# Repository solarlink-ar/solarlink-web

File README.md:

<div align="center">

# Proyecto Solar Link

| Página web | Email | Instagram |
|------------|-------|-----------|
|[Página Web](https://www.solarlink.ar)|info@solarlink.ar|[@solarlink.ar](https://www.instagram.com/solarlink.ar/)|

</div>

## ¿Qué es Solar Link?
&nbsp;&nbsp;&nbsp;&nbsp;&nbsp;&nbsp;Solar Link es un sistema inteligente que optimiza el uso de una energía renovable (por ejemplo, energía solar mediante paneles solares), de manera tal que siempre intentará usar toda la capacidad instalada para ahorrar energía y no consumirla de la red. Es un sistema microprocesado, con conexión a internet y adicionalmente se diseñará una aplicación que  le comunicará al usuario si está ahorrando, cuanto ahorró y una estimación de cuanto ahorrará según el pronóstico del clima.<br>
&nbsp;&nbsp;&nbsp;&nbsp;&nbsp;&nbsp;Dentro los sistemas solares, existen los sistemas *On-grid* y *Off-grid*, mientras que Solar Link es un ***Smart-Grid*** que combina ambos tipos. Este equipo monitorea constantemente el consumo de las líneas eléctricas del hogar y mientras pueda alimentarlas con energía renovables, lo hará posible.<br>
## ¿Cómo ayuda al usuario?
&nbsp;&nbsp;&nbsp;&nbsp;&nbsp;&nbsp;La aplicación móvil que queremos desarrollar le comunicará al usuario toda la información recopilada sobre la red eléctrica. Por ejemplo, podría informar en tiempo real el consumo de la casa, que parte del consumo total de la casa fue proporcionado por energías renovables, o recomendaciones para incrementar el ahorro de energía. De esta manera, el usuario sabrá con certeza el aporte del sistema de energías renovables en el que invirtió.<br>
## ¿Qué aporta a la sociedad?
&nbsp;&nbsp;&nbsp;&nbsp;&nbsp;&nbsp;Consideramos que nuestro proyecto aporta fuertemente a reducir la huella de carbono, ahorrar dinero e incentivar al usuario al uso de este tipo de energías que poco se habla y poco uso hay en Argentina.<br>
## ¿En qué trabajamos?
&nbsp;&nbsp;&nbsp;&nbsp;&nbsp;&nbsp;Nosotros nos encargamos del diseño y la planificación de los diferentes sistemas que forman parte de Solar Link, como el desarrollo íntegro de las placas y los circuitos, la programación del microprocesador, así como la aplicación en su totalidad. Esto conlleva mucho trabajo y esfuerzo de nuestra parte, puesto que siempre buscamos la excelencia en todo lo que hacemos.<br>

## Integrantes:
<div align="center">

</div>

### Iván Ezequiel Cenyko
Programación en microPython y desarrollo web Back-End.

- 📷 Instagram: @ivancenyko

- 📧 ivancenyko@gmail.com

- LinkedIn: [Ivan Cenyko](http://www.linkedin.com/in/ivan-cenyko/)

### Lara Paloma Dias
Desarrollo web Front-End.

- 📷 Instagram: @palo.dias

- 📧 palomadias308@gmail.com

- LinkedIn: [Lara Paloma Dias](http://www.linkedin.com/in/lara-paloma-dias-598bb9288/)

### Mateo Inza Fior
Desarrollo web Front-End y programación en microPython.

- 📷 Instagram: @mateoinzafior

- 📧 mateoinzafior@gmail.com

- LinkedIn: [Mateo Inza Fior](http://www.linkedin.com/in/mateoinzafior/)

### Agustín Palmieri Hise
Desarrollo eléctrico y electrónico íntegro, y documentación.

- 📷 Instagram: @aguspalmieri780

- 📧 aguspalmierihise@gmail.com

- LinkedIn: [Agustin Palmieri Hise](http://www.linkedin.com/in/agustin-palmieri-hise/)

### Maximiliano Nicolás Testa
Programación en C y desarrollo Front-End de la Web-app

- 📷 Instagram: @testa_45

- 📧 maxitesta2012@gmail.com

- LinkedIn: [Maximiliano Testa](http://www.linkedin.com/in/maximiliano-testa/)

## Contactanos

### Instagram: [@solarlink.ar](https://www.instagram.com/solarlink.ar/)

### Pagina web: [solarlink.ar](https://www.solarlink.ar)

### Mail: info@solarlink.ar

### LinkedIn: [Solar Link](https://www.linkedin.com/company/solarlink-ar/?lipi=urn%3Ali%3Apage%3Ad_flagship3_search_srp_all%3BkHWPFMi%2BQiSqZ7LunD5%2FrA%3D%3D)

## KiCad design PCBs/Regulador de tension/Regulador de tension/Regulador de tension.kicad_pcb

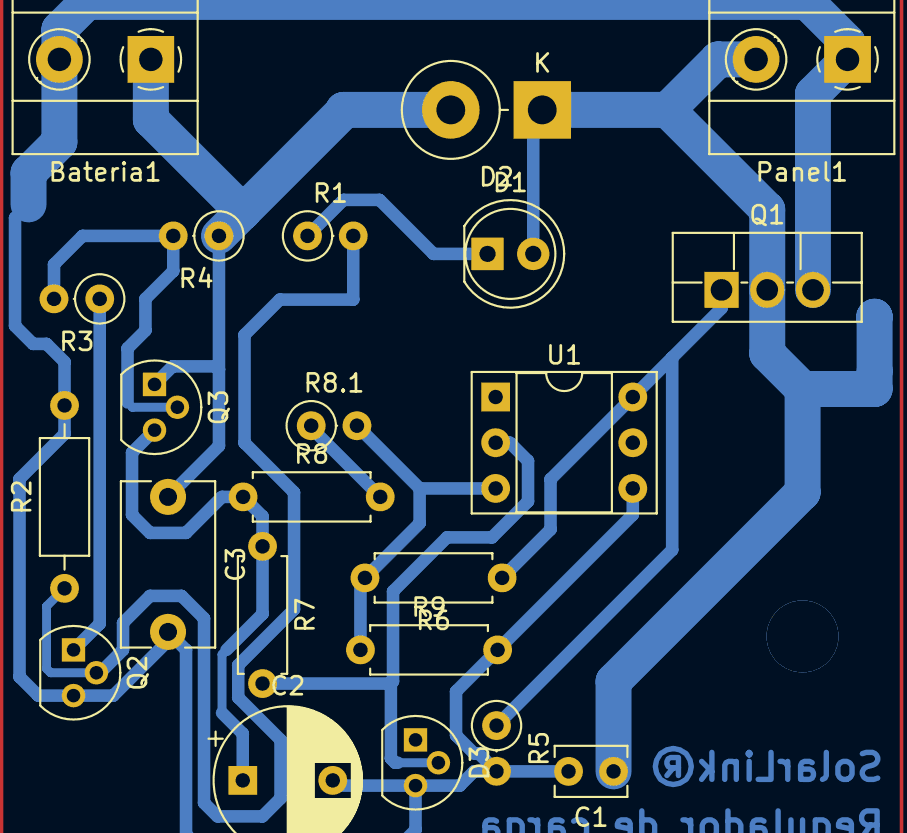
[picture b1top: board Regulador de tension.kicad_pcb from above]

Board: 2 copper layers, 22 parts (0 on the bottom side), 12 nets.

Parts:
Bateria1: Conn_01x02; TerminalBlock_Phoenix_MKDS-1,5-2-5.08_1x02_P5.08mm_Horizont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
C1: 100n; C_Disc_D3.8mm_W2.6mm_P2.50mm
C2: 1000u; CP_Radial_D8.0mm_P5.00mm
C3: 100n; C_Disc_D9.0mm_W5.0mm_P7.50mm
D1: LED; LED_D5.0mm
D2: SB540; D_DO-201AD_P5.08mm_Vertical_KathodeUp
D3: LM385BZ-2.5; TO-92
Panel1: Conn_01x02; TerminalBlock_Phoenix_MKDS-1,5-2-5.08_1x02_P5.08mm_Horizont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
Q1: BUZ11; TO-220F-3_Vertical
Q2: BC548; TO-92
Q3: BC556; TO-92
R1: 1k5; R_Axial_DIN0207_L6.3mm_D2.5mm_P2.54mm_Vertical
R2: 100; R_Axial_DIN0207_L6.3mm_D2.5mm_P10.16mm_Horizontal
R3: 68k; R_Axial_DIN0207_L6.3mm_D2.5mm_P2.54mm_Vertical
R4, R5, R8.1: 10k; R_Axial_DIN0207_L6.3mm_D2.5mm_P2.54mm_Vertical
R6: 22Ok; R_Axial_DIN0207_L6.3mm_D2.5mm_P7.62mm_Horizontal
R7: 100k; R_Axial_DIN0207_L6.3mm_D2.5mm_P7.62mm_Horizontal
R8: 82k; R_Axial_DIN0207_L6.3mm_D2.5mm_P7.62mm_Horizontal
R9: 22k; R_Axial_DIN0207_L6.3mm_D2.5mm_P7.62mm_Horizontal
U1: TLC271; DIP-6_W7.62mm_Socket

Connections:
GND: Bateria1.2, C1.2, C2.2, C3.2, D3.3 (A), Panel1.1, Q1.3 (S), Q2.3 (E), R2.2, R5.2, R9.2, U1.4 (V-)
unnamed: Bateria1.1, C3.1, D2.2 (A), Q3.1 (C), R4.1
unnamed: C1.1, D1.2 (A), D2.1 (K), Panel1.2, Q1.2 (D)
unnamed: C2.1, Q3.3 (E), R7.1, R8.1
unnamed: D1.1 (K), R1.1
unnamed: D3.2 (K), R7.2, U1.2 (-)
unnamed: Q1.1 (G), R5.1, R6.1, U1.6
unnamed: Q2.1 (C), R3.1
unnamed: Q2.2 (B), R1.2, R2.1
unnamed: Q3.2 (B), R3.2, R4.2
unnamed: R8.2, R8.1.1
unnamed: R6.2, R8.1.2, R9.1, U1.3 (+)

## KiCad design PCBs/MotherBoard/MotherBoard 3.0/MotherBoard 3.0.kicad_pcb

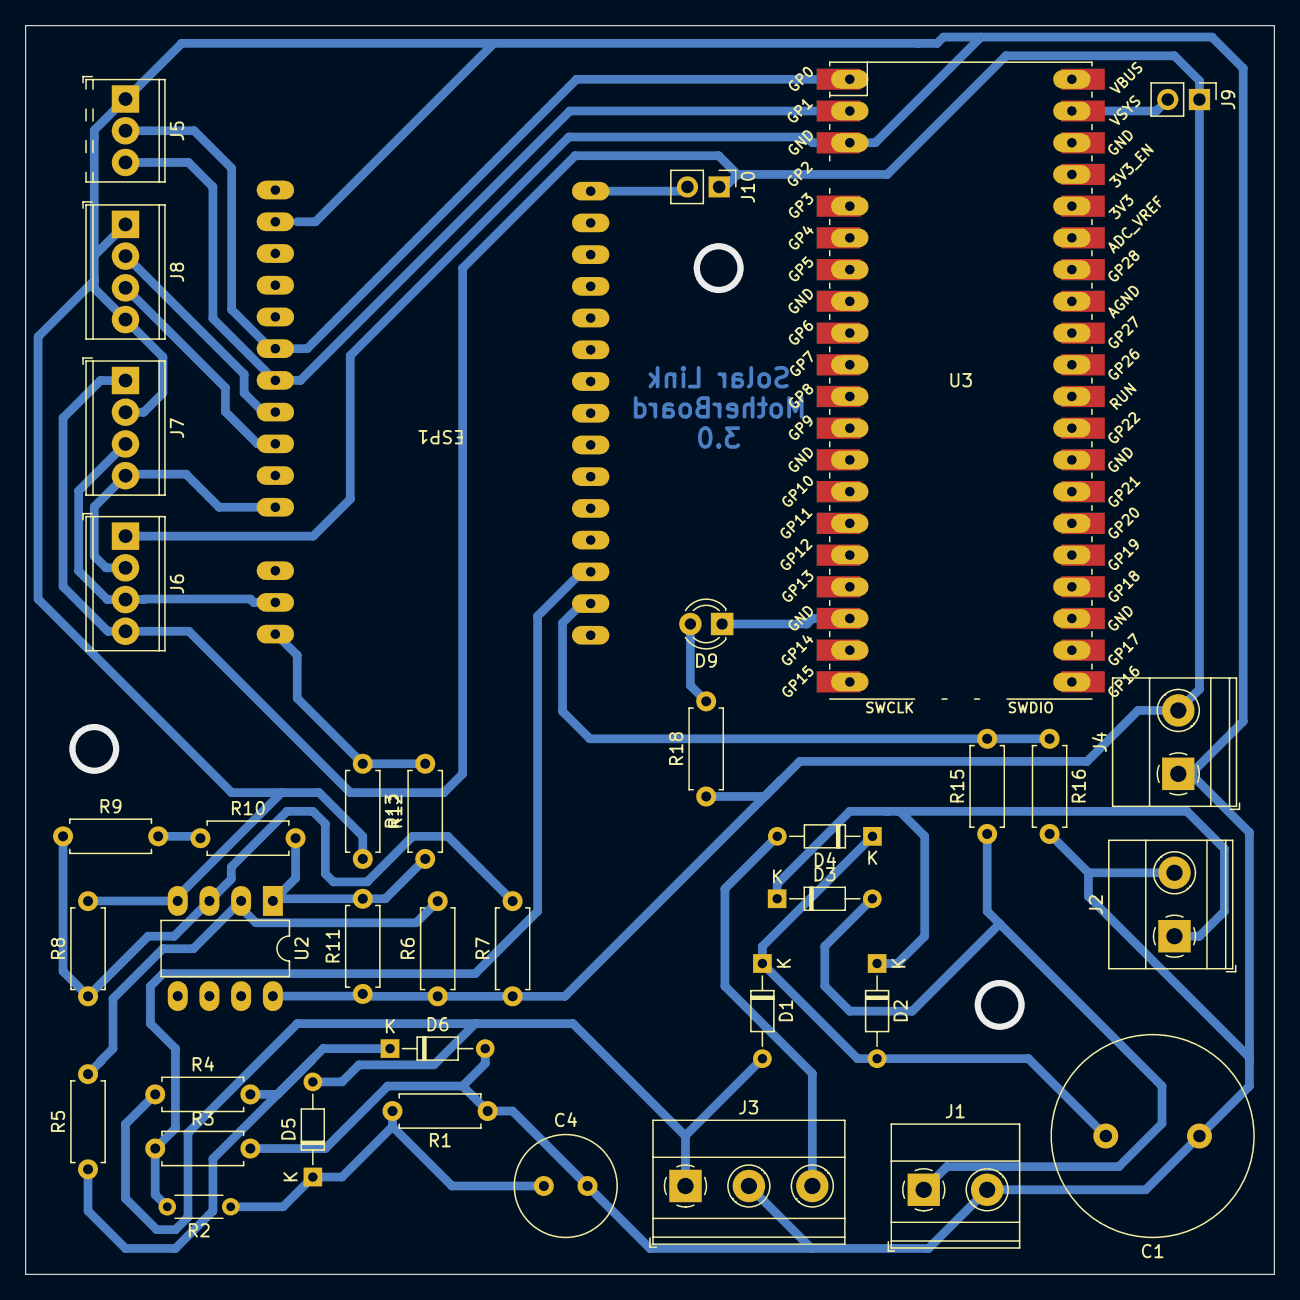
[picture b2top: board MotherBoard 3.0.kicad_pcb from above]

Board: 2 copper layers, 100.0 x 100.0 mm, 38 parts (0 on the bottom side), 26 nets.

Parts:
C1: 2200uF; C_Radial_D16.0mm_H25.0mm_P7.50mm
C4: 100u; C_Radial_D8.0mm_H11.5mm_P3.50mm
D1, D2, D3, D4, D5: D; D_DO-34_SOD68_P7.62mm_Horizontal
D6: 1N914; D_DO-34_SOD68_P7.62mm_Horizontal
D9: Verde; LED_D3.0mm
ESP1: ESP32 15pin
J1: Bateria; TerminalBlock_Phoenix_MKDS-1,5-2-5.08_1x02_P5.08mm_Horizont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
J2: Salida 12V; TerminalBlock_Phoenix_MKDS-1,5-2-5.08_1x02_P5.08mm_Horizont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
J3: Transformador; TerminalBlock_Phoenix_MKDS-1,5-3-5.08_1x03_P5.08mm_Horizont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
J4: Salida 5v; TerminalBlock_Phoenix_MKDS-1,5-2-5.08_1x02_P5.08mm_Horizont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
J5: Raspberry Pi; TerminalBlock_Phoenix_MPT-0,5-3-2.54_1x03_P2.54mm_Horizontal
J6: LCD; TerminalBlock_Phoenix_MPT-0,5-4-2.54_1x04_P2.54mm_Horizontal
J7: Corriente; TerminalBlock_Phoenix_MPT-0,5-4-2.54_1x04_P2.54mm_Horizontal
J8: Conmutacion; TerminalBlock_Phoenix_MPT-0,5-4-2.54_1x04_P2.54mm_Horizontal
J9, J10: Conn_01x02_Pin; PinHeader_1x02_P2.54mm_Vertical
R1, R3, R8, R16: 10k; R_Axial_DIN0207_L6.3mm_D2.5mm_P7.62mm_Horizontal
R2: 220k; R_Axial_DIN0204_L3.6mm_D1.6mm_P5.08mm_Horizontal
R4, R5, R11: 5,1k; R_Axial_DIN0207_L6.3mm_D2.5mm_P7.62mm_Horizontal
R6, R7, R12, R15: 100k; R_Axial_DIN0207_L6.3mm_D2.5mm_P7.62mm_Horizontal
R9, R10: 10M; R_Axial_DIN0207_L6.3mm_D2.5mm_P7.62mm_Horizontal
R13: 150k; R_Axial_DIN0207_L6.3mm_D2.5mm_P7.62mm_Horizontal
R18: 1k; R_Axial_DIN0207_L6.3mm_D2.5mm_P7.62mm_Horizontal
U2: AD8603; DIP-8_W7.62mm_LongPads
U3: Pico; RPi_Pico_SMD_TH

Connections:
Bat 1: D3.2 (A), J1.1, R15.1
Bat 2: C1.1, C4.2, D6.2 (A), ESP1.29 (GPIO0,RTC_GPIO11,ADC2_1,TOUCH_1), J1.2, J2.2, J3.2, J4.1, J5.1, J6.1, J7.2, J8.1, J8.4, R1.1, R3.2, R8.2, R13.2, R16.2, U2.4 (V-), U3.3 (GND)
ESP1, ADC: ESP1.3 (ADC1_0,RTC_GPIO0,GPIO36), R2.2, R3.1
ESP2: ESP1.16 (GND), R12.2, R13.1
ESP3, I/O: ESP1.23 (GPIO19,VSPI_MISO), J8.2
ESP4, I/O: ESP1.22 (GND), J8.3
ESP5, SDA: ESP1.20 (GPIO3,RX0), J6.2, J7.4
ESP6, SCL: ESP1.17 (GPIO23,VSPI_MOSI), J6.3, J7.3
ESP7, Rx: ESP1.25 (GPIO5,VSPI_CS), J5.2, U3.1 (GPIO0)
ESP8, Tx: ESP1.24 (GPIO18,VSPI_CLK), J5.3, U3.2 (GPIO1)
ESP 12, ADC: ESP1.2 (Reset,En), R15.2, R16.1
Fuente 5v: J4.2, J6.4, J7.1, J9.1, J10.1, R6.1, R7.1, R11.1, R18.1, U2.8 (V+)
Fuente 12v: D2.1 (K), D3.1 (K), J2.1
GNDREF: D9.1 (K), U3.18 (GND)
unnamed: C1.2, D1.1 (K), D2.2 (A), D4.1 (K)
unnamed: C4.1, D5.1 (K), R1.2, R2.1
unnamed: D6.1 (K), R4.2, R5.1
unnamed: D9.2 (A), R18.2
unnamed: ESP1.15 (ADC2_4,RTCGPIO14,GPIO13,TOUCH_4,HSPI_MO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), J10.2
unnamed: J9.2, U3.39 (VSYS)
unnamed: R9.2, R10.1
unnamed: R10.2, R11.2, R12.1, U2.1
unnamed: R7.2, R8.1, R9.1, U2.3 (+)
unnamed: R5.2, R6.2, U2.2 (-)
Trans 1: D1.2 (A), D5.2 (A), J3.1, R4.1
Trans 2: D4.2 (A), J3.3

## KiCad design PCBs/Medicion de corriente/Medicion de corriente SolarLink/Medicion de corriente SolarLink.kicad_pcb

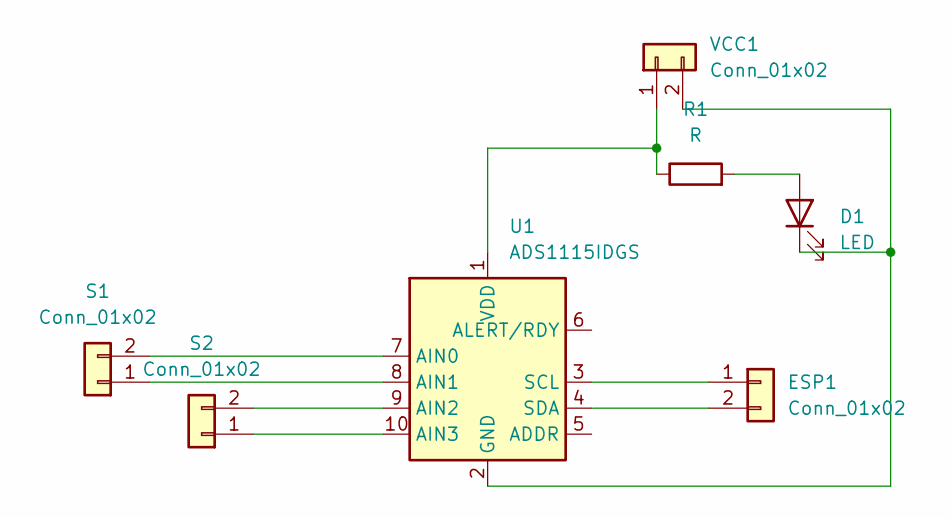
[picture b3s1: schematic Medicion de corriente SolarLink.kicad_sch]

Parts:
D1: LED; LED_D3.0mm
ESP1: Conn_01x02; JST_XH_B2B-XH-AM_1x02_P2.50mm_Vertical
R1: R; R_Axial_DIN0204_L3.6mm_D1.6mm_P5.08mm_Horizontal
S1, S2: Conn_01x02; PinHeader_1x02_P2.54mm_Vertical
U1: ADS1115IDGS; PinHeader_1x10_P2.54mm_Vertical
VCC1: Conn_01x02; JST_XH_B2B-XH-AM_1x02_P2.50mm_Vertical

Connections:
GND: R1.1, U1.1 (VDD), VCC1.1
unnamed: D1.1 (K), U1.2 (GND), VCC1.2
unnamed: D1.2 (A), R1.2
unnamed: ESP1.1, U1.3 (SCL)
unnamed: ESP1.2, U1.4 (SDA)
unnamed: S1.1, U1.8 (AIN1)
unnamed: S1.2, U1.7 (AIN0)
unnamed: S2.1, U1.10 (AIN3)
unnamed: S2.2, U1.9 (AIN2)

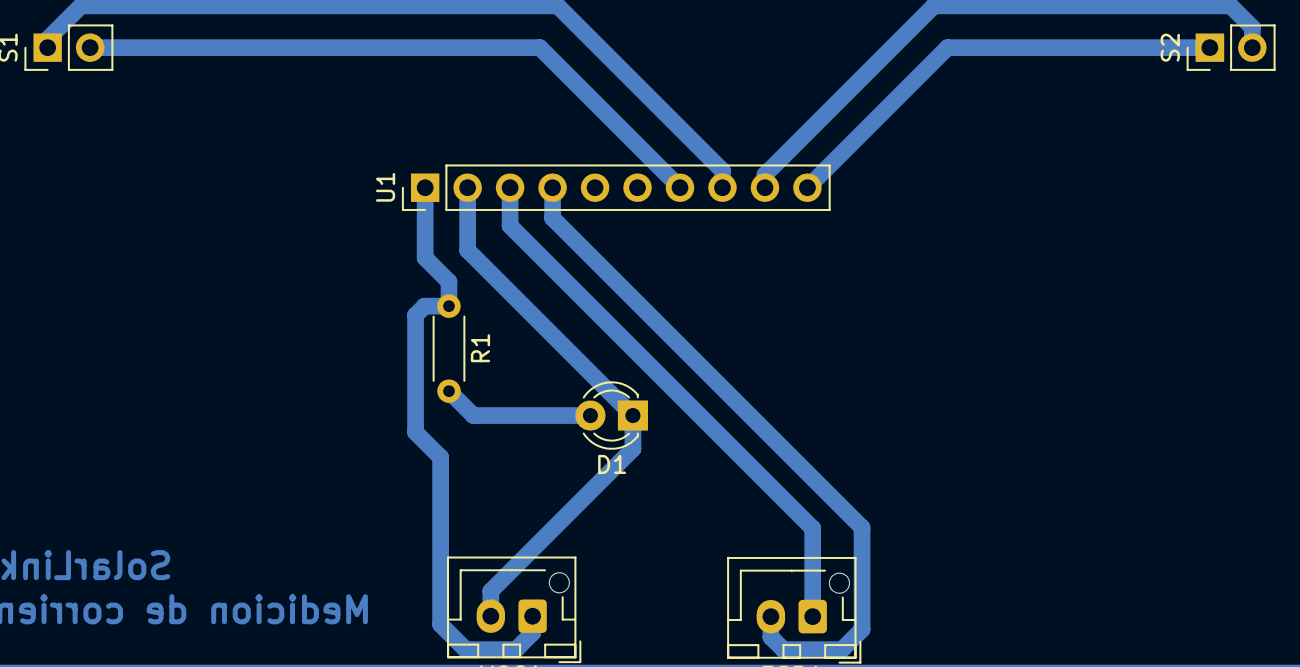
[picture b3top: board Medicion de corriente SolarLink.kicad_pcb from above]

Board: 2 copper layers, 7 parts (0 on the bottom side), 9 nets.

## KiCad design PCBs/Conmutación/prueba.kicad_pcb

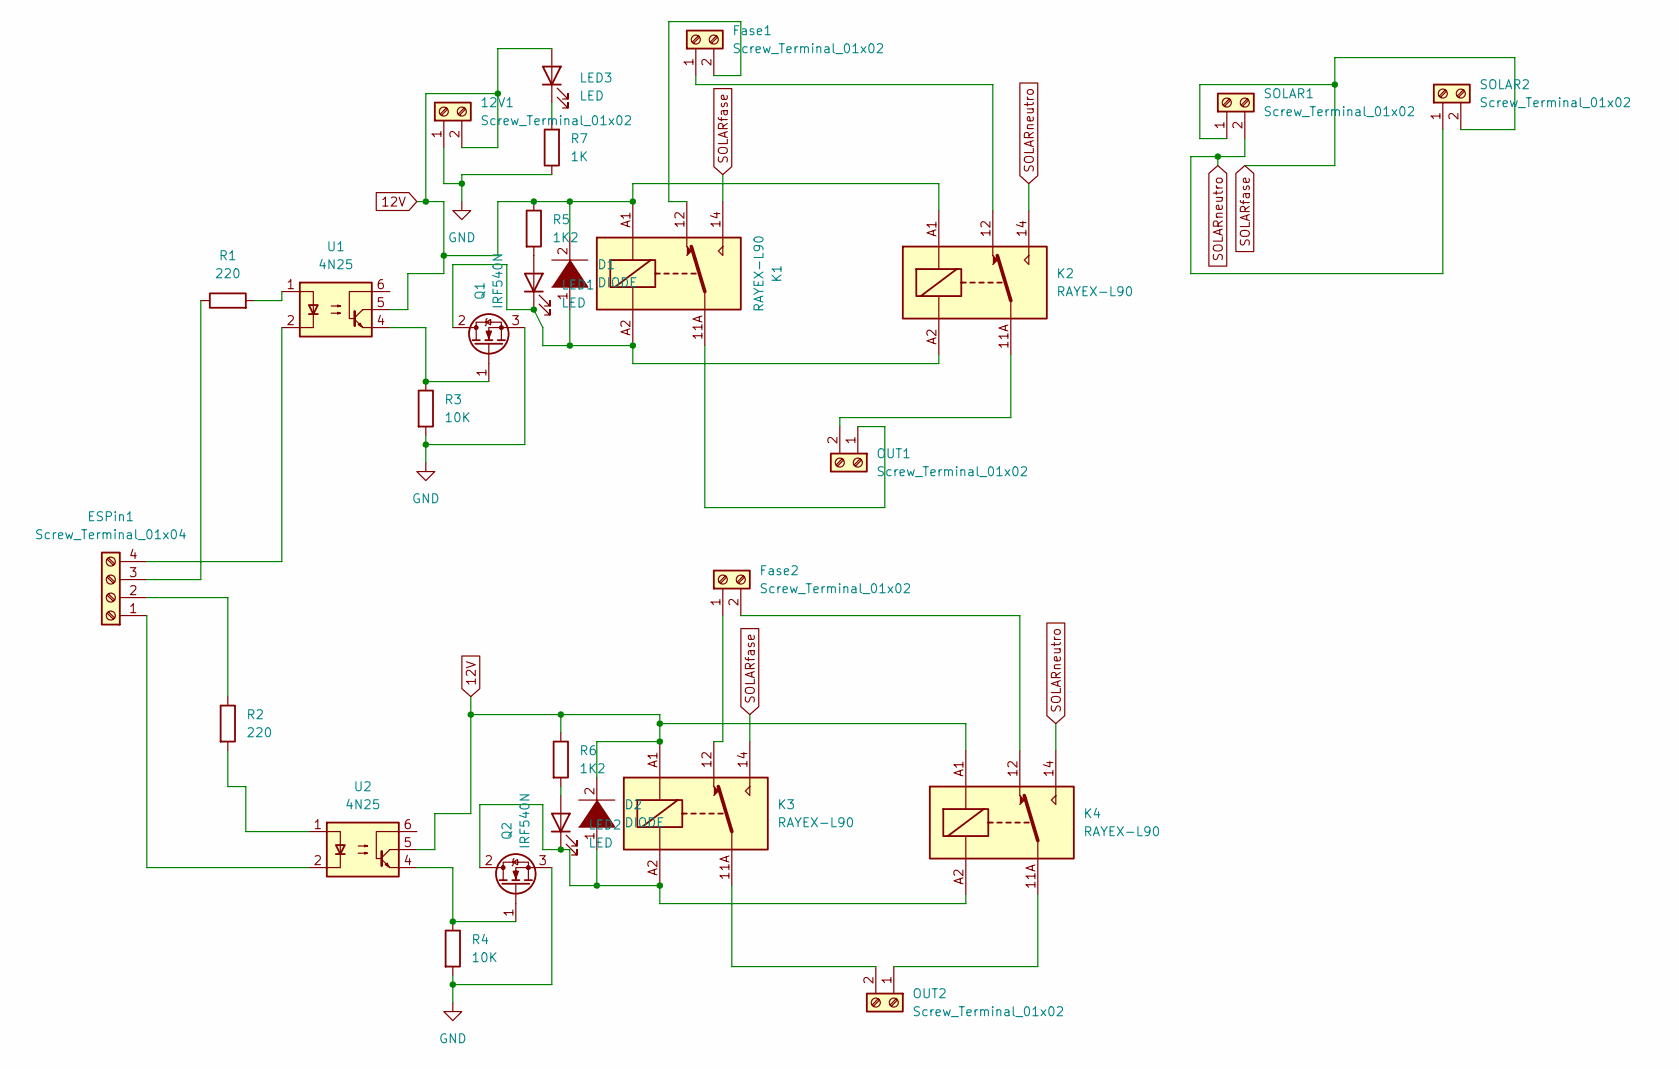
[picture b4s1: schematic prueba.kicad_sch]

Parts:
12V1: Screw_Terminal_01x02; TerminalBlock_Phoenix_MKDS-1,5-2-5.08_1x02_P5.08mm_Horizont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
D1, D2: DIODE; D_DO-201AD_P5.08mm_Vertical_AnodeUp
ESPin1: Screw_Terminal_01x04; TerminalBlock_Phoenix_MPT-0,5-4-2.54_1x04_P2.54mm_Horizontal
Fase1, Fase2: Screw_Terminal_01x02; TerminalBlock_MetzConnect_Type067_RT01902HDWC_1x02_P10.00mm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
K1, K2, K3, K4: RAYEX-L90; Relay_SPDT_RAYEX-L90
LED1, LED2, LED3: LED; LED_D5.0mm
OUT1, OUT2: Screw_Terminal_01x02; TerminalBlock_MetzConnect_Type067_RT01902HDWC_1x02_P10.00mm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
Q1, Q2: IRF540N; TO-220-3_Vertical
R1, R2: 220; R_Axial_DIN0207_L6.3mm_D2.5mm_P7.62mm_Horizontal
R3, R4: 10K; R_Axial_DIN0411_L9.9mm_D3.6mm_P5.08mm_Vertical
R5, R6: 1K2; R_Axial_DIN0207_L6.3mm_D2.5mm_P2.54mm_Vertical
R7: 1K; R_Axial_DIN0207_L6.3mm_D2.5mm_P2.54mm_Vertical
SOLAR1, SOLAR2: Screw_Terminal_01x02; TerminalBlock_MetzConnect_Type067_RT01902HDWC_1x02_P10.00mm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
U1, U2: 4N25; DIP-6_W7.62mm

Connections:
12V: 12V1.2, D1.2 (A), D2.2 (A), K1.A1, K2.A1, K3.A1, K4.A1, LED3.2 (A), R5.1, R6.1, U1.5, U2.5
GND: 12V1.1, Q1.3 (S), Q2.3 (S), R3.2, R4.2, R7.1
unnamed: D1.1 (K), K1.A2, K2.A2, LED1.1 (K), Q1.2 (D)
unnamed: D2.1 (K), K3.A2, K4.A2, LED2.1 (K), Q2.2 (D)
unnamed: ESPin1.1, U2.2
unnamed: ESPin1.2, R2.1
unnamed: ESPin1.3, R1.1
unnamed: ESPin1.4, U1.2
unnamed: Fase1.2, K1.12
unnamed: Fase2.1, K3.12
unnamed: Fase2.2, K4.12
unnamed: K2.11A, K2.11B, OUT1.2
unnamed: Fase1.1, K2.12
unnamed: K3.11A, K3.11B, OUT2.2
unnamed: K4.11A, K4.11B, OUT2.1
unnamed: LED1.2 (A), R5.2
unnamed: LED2.2 (A), R6.2
unnamed: LED3.1 (K), R7.2
unnamed: K1.11A, K1.11B, OUT1.1
unnamed: Q1.1 (G), R3.1, U1.4
unnamed: Q2.1 (G), R4.1, U2.4
unnamed: R1.2, U1.1
unnamed: R2.2, U2.1
SOLARfase: K1.14, K3.14, SOLAR1.1, SOLAR2.2
SOLARneutro: K2.14, K4.14, SOLAR1.2, SOLAR2.1

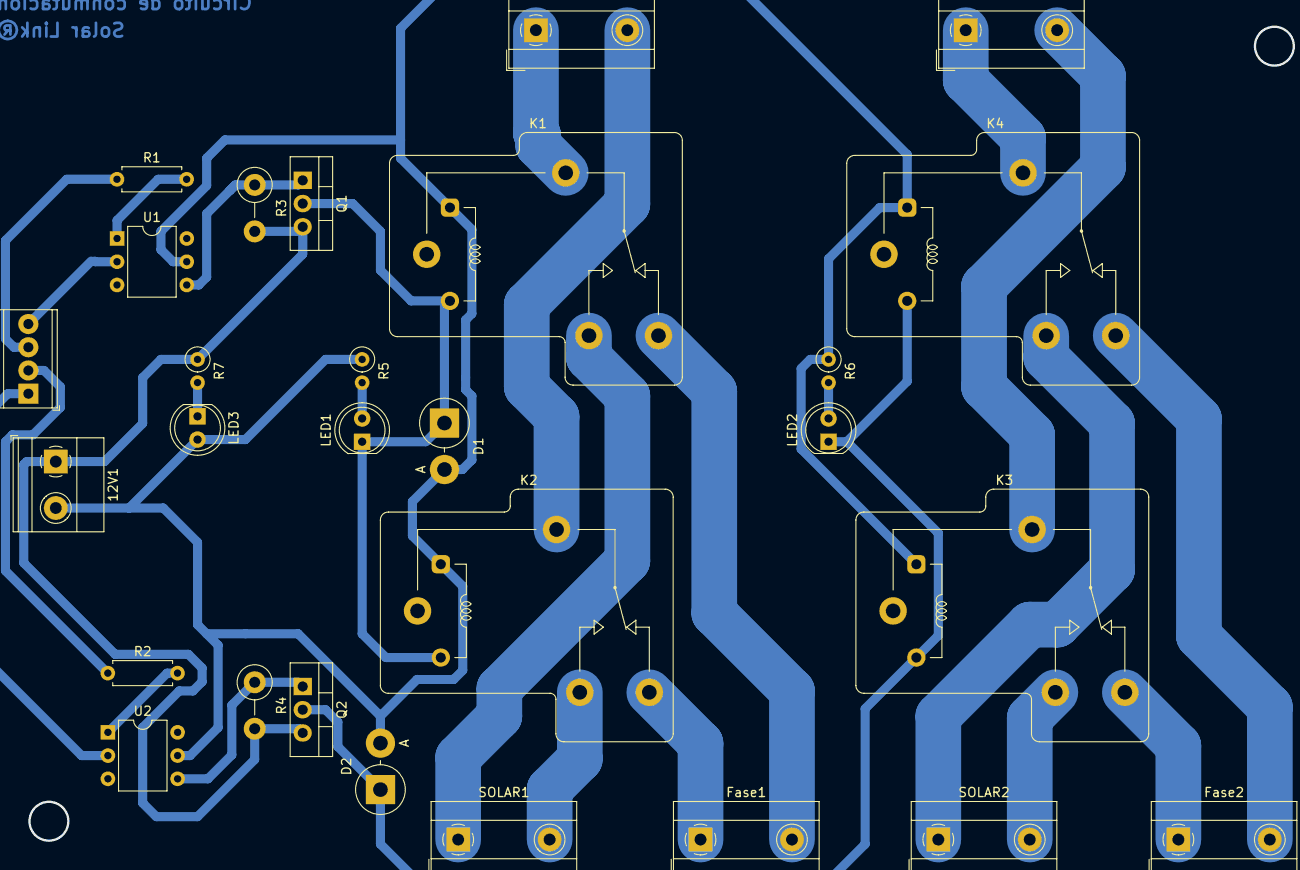
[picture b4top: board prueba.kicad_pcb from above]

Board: 2 copper layers, 28 parts (0 on the bottom side), 25 nets.

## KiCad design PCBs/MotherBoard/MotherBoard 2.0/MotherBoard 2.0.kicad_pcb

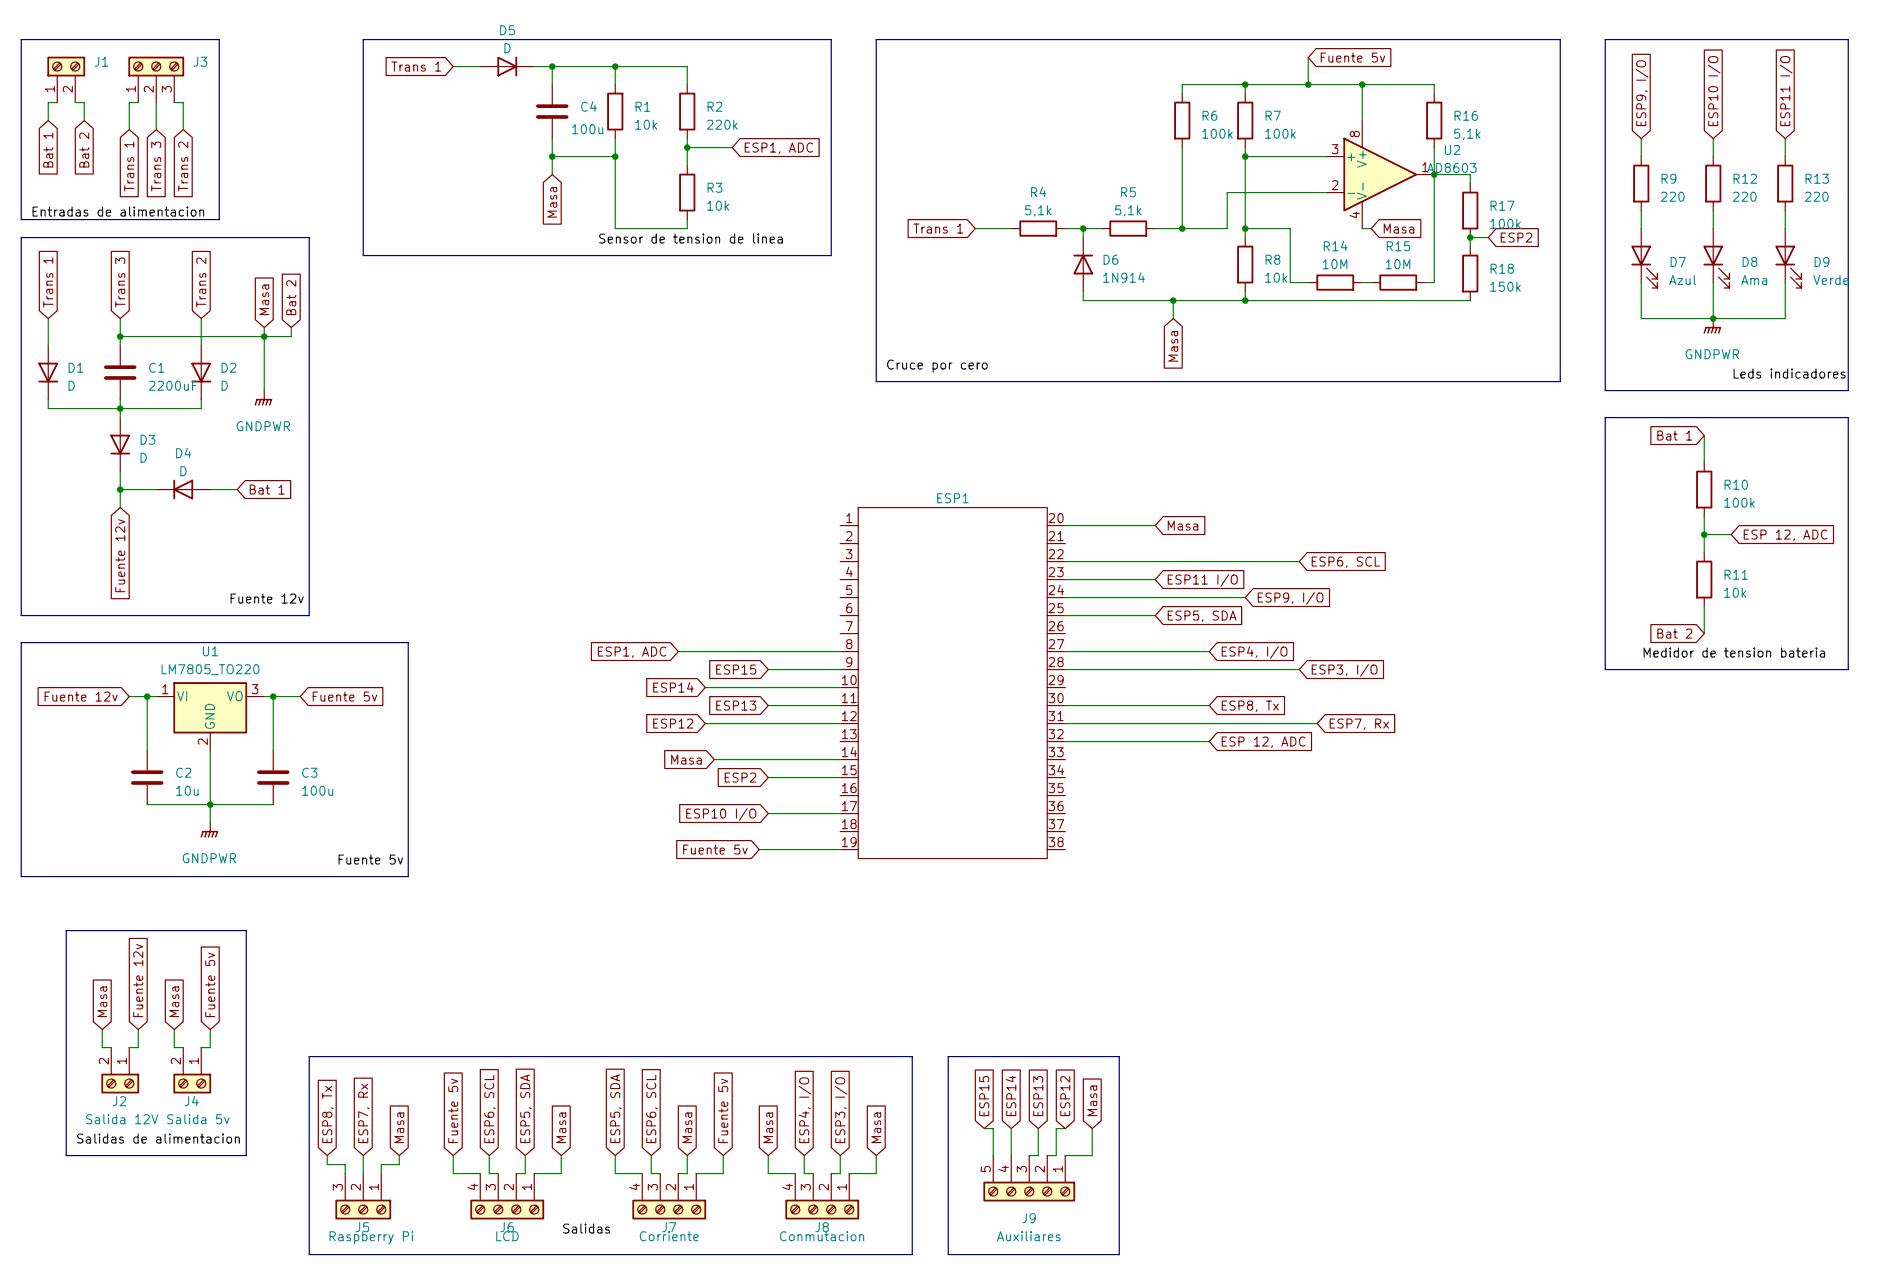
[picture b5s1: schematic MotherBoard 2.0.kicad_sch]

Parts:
C1: 2200uF; C_Radial_D16.0mm_H25.0mm_P7.50mm
C2: 10u; C_Radial_D6.3mm_H11.0mm_P2.50mm
C3, C4: 100u; C_Radial_D8.0mm_H11.5mm_P3.50mm
D1, D2, D3, D4, D5: D; D_DO-34_SOD68_P7.62mm_Horizontal
D6: 1N914; D_DO-34_SOD68_P7.62mm_Horizontal
D7: Azul; LED_D3.0mm
D8: Ama; LED_D3.0mm
D9: Verde; LED_D3.0mm
ESP1: ESP32 NODEMCU
J1: Bateria; TerminalBlock_Phoenix_MKDS-1,5-2-5.08_1x02_P5.08mm_Horizont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
J2: Salida 12V; TerminalBlock_Phoenix_MKDS-1,5-2-5.08_1x02_P5.08mm_Horizont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
J3: Transformador; TerminalBlock_Phoenix_MKDS-1,5-3-5.08_1x03_P5.08mm_Horizont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
J4: Salida 5v; TerminalBlock_Phoenix_MKDS-1,5-2-5.08_1x02_P5.08mm_Horizont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
J5: Raspberry Pi; TerminalBlock_Phoenix_MPT-0,5-3-2.54_1x03_P2.54mm_Horizontal
J6: LCD; TerminalBlock_Phoenix_MPT-0,5-4-2.54_1x04_P2.54mm_Horizontal
J7: Corriente; TerminalBlock_Phoenix_MPT-0,5-4-2.54_1x04_P2.54mm_Horizontal
J8: Conmutacion; TerminalBlock_Phoenix_MPT-0,5-4-2.54_1x04_P2.54mm_Horizontal
J9: Auxiliares; TerminalBlock_Phoenix_MPT-0,5-5-2.54_1x05_P2.54mm_Horizontal
R1, R3, R8, R11: 10k; R_Axial_DIN0207_L6.3mm_D2.5mm_P7.62mm_Horizontal
R2: 220k; R_Axial_DIN0204_L3.6mm_D1.6mm_P5.08mm_Horizontal
R4, R5, R16: 5,1k; R_Axial_DIN0207_L6.3mm_D2.5mm_P7.62mm_Horizontal
R6, R7, R10, R17: 100k; R_Axial_DIN0207_L6.3mm_D2.5mm_P7.62mm_Horizontal
R9, R12, R13: 220; R_Axial_DIN0207_L6.3mm_D2.5mm_P7.62mm_Horizontal
R14, R15: 10M; R_Axial_DIN0207_L6.3mm_D2.5mm_P7.62mm_Horizontal
R18: 150k; R_Axial_DIN0207_L6.3mm_D2.5mm_P7.62mm_Horizontal
U1: LM7805_TO220; TO-220-3_Vertical
U2: AD8603; DIP-8_W7.62mm_LongPads

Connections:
Bat 1: D4.2 (A), J1.1, R10.1
Bat 2: C1.1, C2.2, C3.2, C4.2, D6.2 (A), D7.1 (K), D8.1 (K), D9.1 (K), ESP1.14 (GND), ESP1.20 (GND), J1.2, J2.2, J3.2, J4.2, J5.1, J6.1, J7.2, J8.1, J8.4, J9.1, R1.1, R3.2, R8.2, R11.2, R18.2, U1.2 (GND), U2.4 (V-)
ESP1, ADC: ESP1.8 (ADC1_5,RTCGPIO8,GPIO33,TOUCH_8), R2.2, R3.1
ESP2: ESP1.15 (ADC2_4,RTCGPIO14,GPIO13,TOUCH_4,HSPI_MO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), R17.2, R18.1
ESP3, I/O: ESP1.28 (GPIO18,VSPI_CLK), J8.2
ESP4, I/O: ESP1.27 (GPIO19,VSPI_MISO), J8.3
ESP5, SDA: ESP1.25 (GPIO21,I2C_SDA), J6.2, J7.4
ESP6, SCL: ESP1.22 (GPIO22,I2C_SCL), J6.3, J7.3
ESP7, Rx: ESP1.31 (GPIO16,RX2), J5.2
ESP8, Tx: ESP1.30 (GPIO17,TX2), J5.3
ESP9, I/O: ESP1.24 (GPIO3,RX0), R9.1
ESP10 I/O: ESP1.17 (SWP/SD3,GPIO10), R12.1
ESP11 I/O: ESP1.23 (GPIO1,TX0), R13.1
ESP12: ESP1.12 (ADC2_6,RTCGPIO16,GPIO32,TOUCH_6,HSPI_CL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), J9.2
ESP13: ESP1.11 (ADC2_7,RTCGPIO17,GPIO27,TOUCH_7), J9.3
ESP14: ESP1.10 (ADC2_9,RTCGPIO7,GPIO26,DAC_2), J9.4
ESP15: ESP1.9 (ADC2_8,RTCGPIO8,GPIO25,DAC_1), J9.5
ESP 12, ADC: ESP1.32 (GPIO4,RTC_GPIO10,ADC2_0,TOUCH_0,SD_DAT1), R10.2, R11.1
Fuente 5v: C3.1, ESP1.19 (5v), J4.1, J6.4, J7.1, R6.1, R7.1, R16.1, U1.3 (VO), U2.8 (V+)
Fuente 12v: C2.1, D3.1 (K), D4.1 (K), J2.1, U1.1 (VI)
unnamed: C1.2, D1.1 (K), D2.1 (K), D3.2 (A)
unnamed: C4.1, D5.1 (K), R1.2, R2.1
unnamed: D6.1 (K), R4.2, R5.1
unnamed: D7.2 (A), R9.2
unnamed: D8.2 (A), R12.2
unnamed: D9.2 (A), R13.2
unnamed: R14.2, R15.1
unnamed: R15.2, R16.2, R17.1, U2.1
unnamed: R7.2, R8.1, R14.1, U2.3 (+)
unnamed: R5.2, R6.2, U2.2 (-)
Trans 1: D1.2 (A), D5.2 (A), J3.1, R4.1
Trans 2: D2.2 (A), J3.3

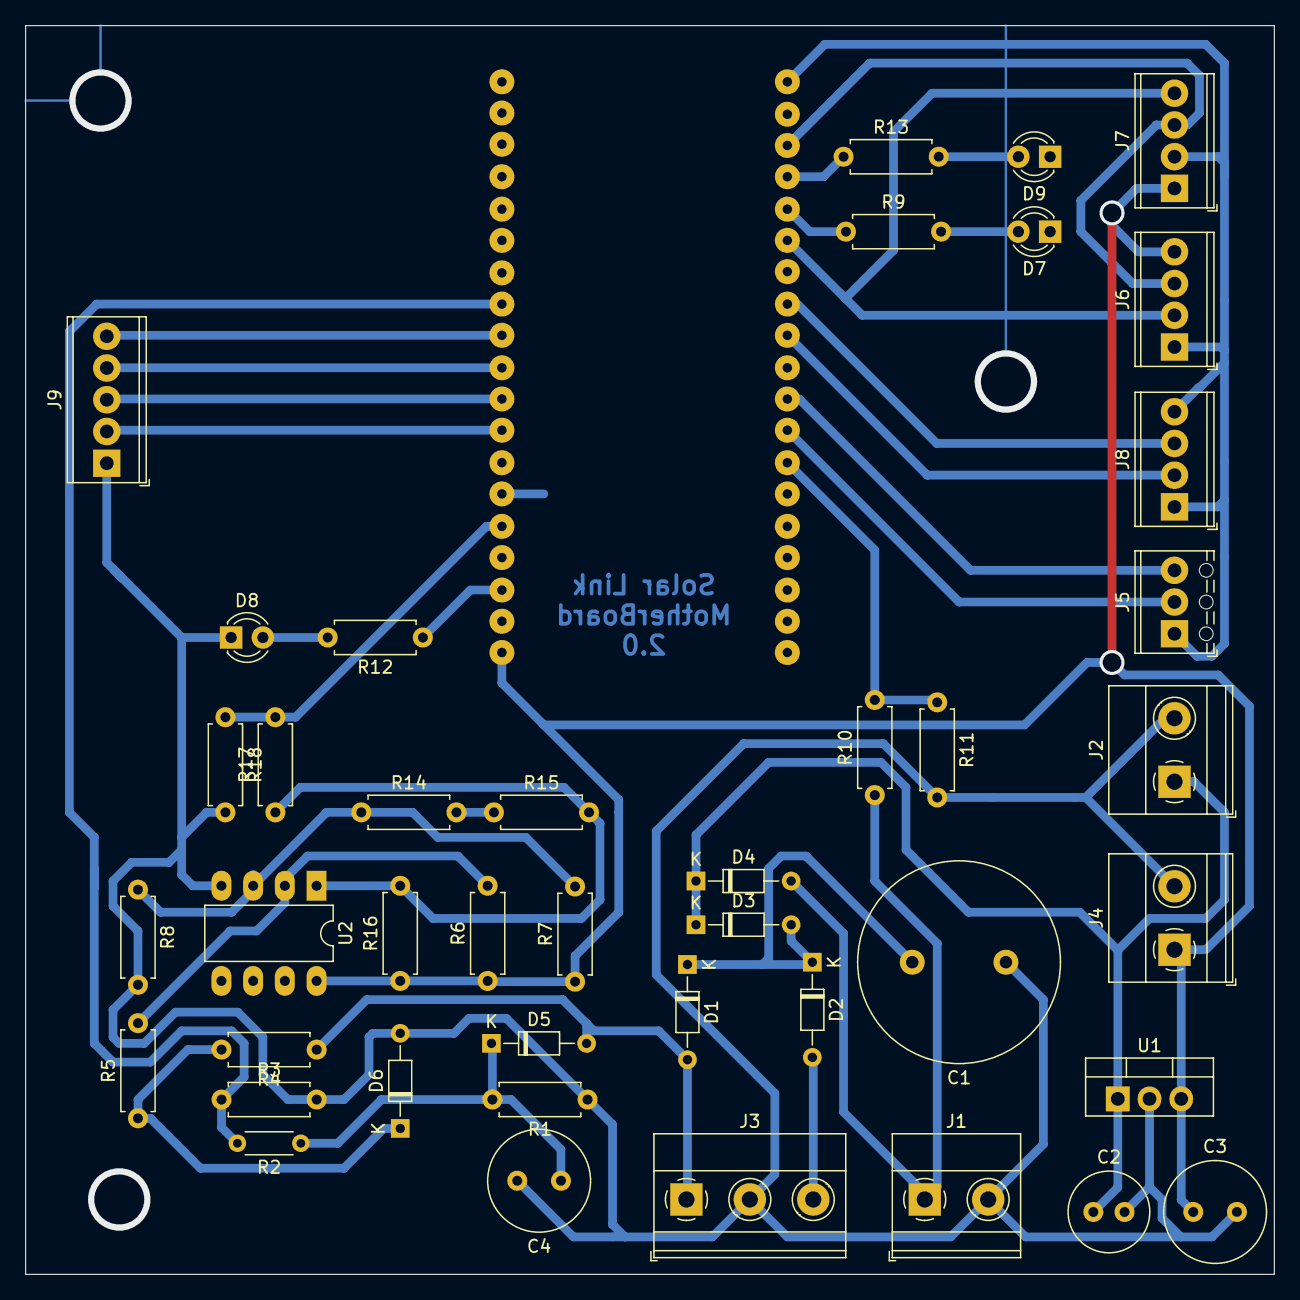
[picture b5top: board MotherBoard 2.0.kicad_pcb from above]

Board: 2 copper layers, 100.0 x 100.0 mm, 43 parts (0 on the bottom side), 32 nets.

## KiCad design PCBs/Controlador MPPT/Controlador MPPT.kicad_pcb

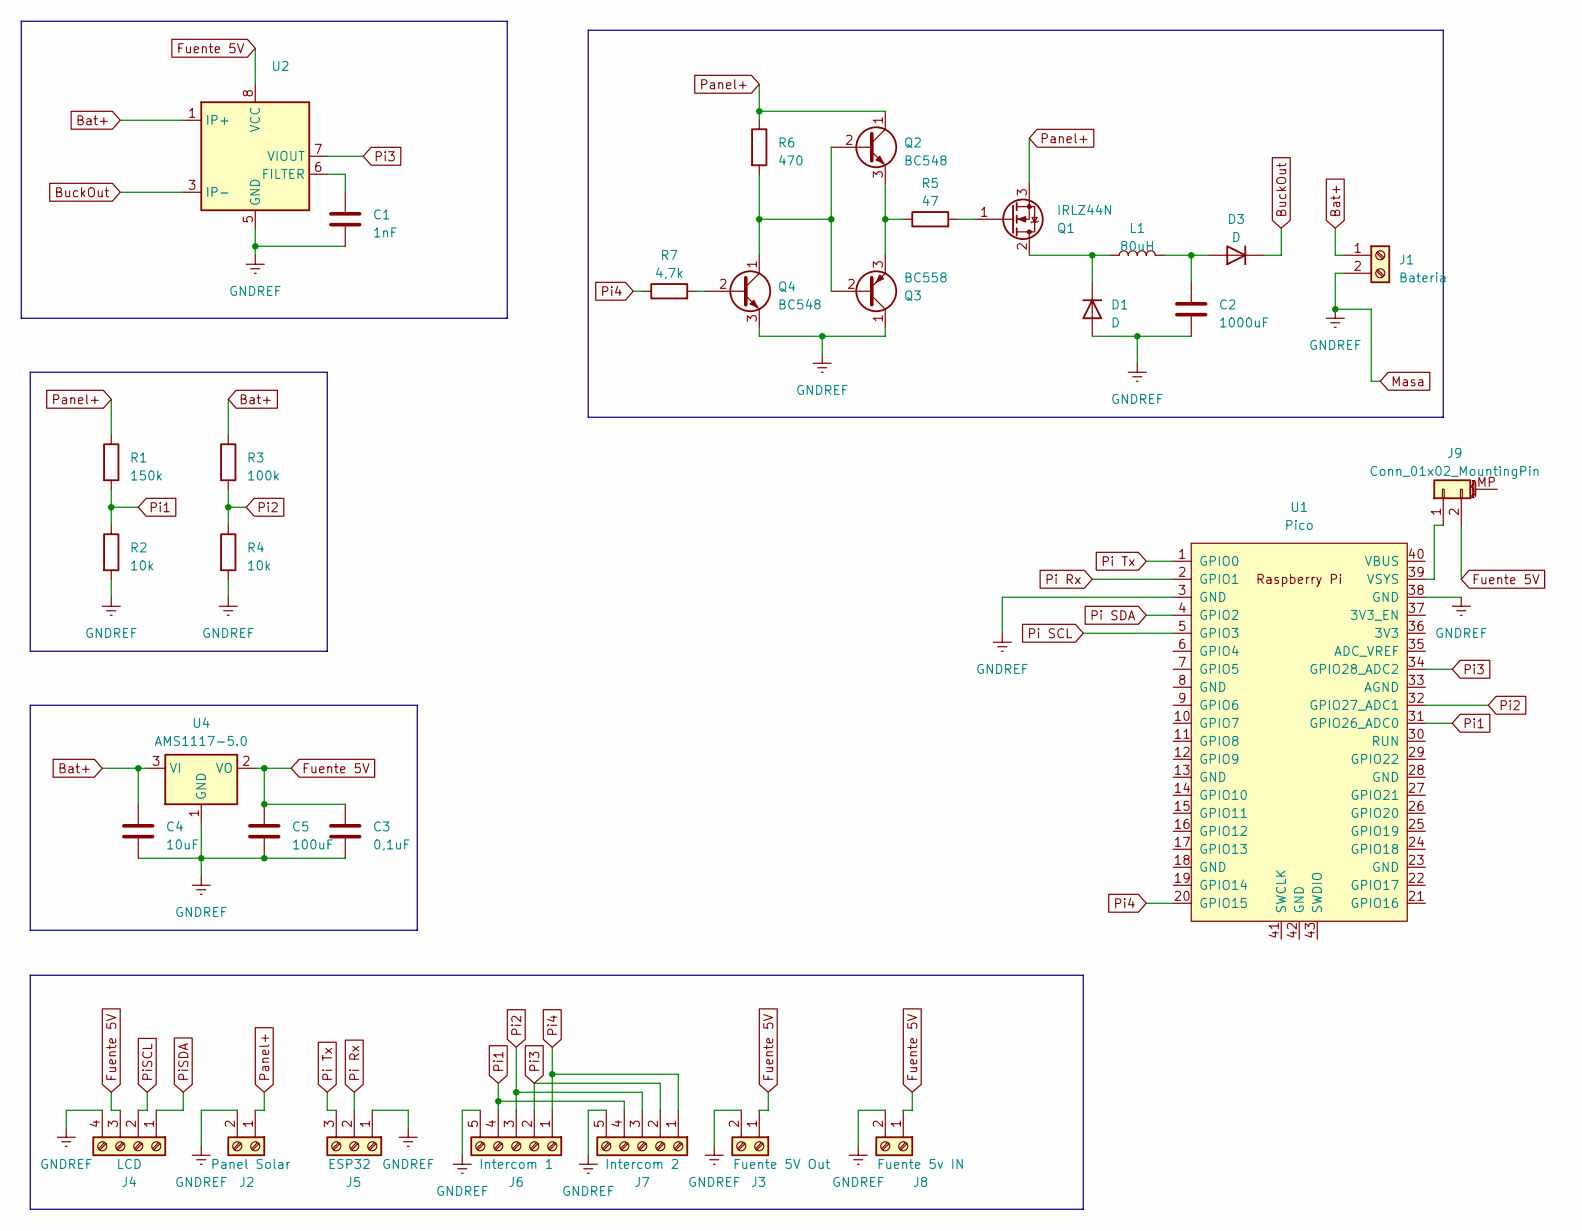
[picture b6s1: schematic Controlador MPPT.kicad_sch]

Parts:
C1: 1nF; C_Disc_D3.0mm_W1.6mm_P2.50mm
C2: 1000uF; C_Radial_D12.5mm_H25.0mm_P5.00mm
C3: 0,1uF; C_Disc_D3.0mm_W1.6mm_P2.50mm
C4: 10uF; C_Radial_D6.3mm_H11.0mm_P2.50mm
C5: 100uF; C_Radial_D8.0mm_H11.5mm_P3.50mm
D1, D3: D; TO-3P-3_Vertical
J1: Bateria; TerminalBlock_MetzConnect_Type067_RT01902HDWC_1x02_P10.00mm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
J2: Panel Solar; TerminalBlock_MetzConnect_Type067_RT01902HDWC_1x02_P10.00mm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
J3: Fuente 5V Out; TerminalBlock_Phoenix_MKDS-1,5-2-5.08_1x02_P5.08mm_Horizont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
J4: LCD; TerminalBlock_Phoenix_MPT-0,5-4-2.54_1x04_P2.54mm_Horizontal
J5: ESP32; TerminalBlock_Phoenix_MPT-0,5-3-2.54_1x03_P2.54mm_Horizontal
J6: Intercom 1; TerminalBlock_Phoenix_MPT-0,5-5-2.54_1x05_P2.54mm_Horizontal
J7: Intercom 2; TerminalBlock_Phoenix_MPT-0,5-5-2.54_1x05_P2.54mm_Horizontal
J8: Fuente 5v IN; TerminalBlock_Phoenix_MKDS-1,5-2-5.08_1x02_P5.08mm_Horizont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
J9: Conn_01x02_MountingPin; PinHeader_1x02_P2.54mm_Vertical
L1: 80uH; L_Toroid_Horizontal_D41.9mm_P37.60mm_Vishay_TJ7
Q1: IRLZ44N; TO-220-3_Vertical
Q2, Q4: BC548; TO-92_Inline_Wide
Q3: BC558; TO-92_Inline_Wide
R1: 150k; R_Axial_DIN0207_L6.3mm_D2.5mm_P7.62mm_Horizontal
R2, R4: 10k; R_Axial_DIN0207_L6.3mm_D2.5mm_P7.62mm_Horizontal
R3: 100k; R_Axial_DIN0207_L6.3mm_D2.5mm_P15.24mm_Horizontal
R5: 47; R_Axial_DIN0207_L6.3mm_D2.5mm_P7.62mm_Horizontal
R6: 470; R_Axial_DIN0207_L6.3mm_D2.5mm_P7.62mm_Horizontal
R7: 4,7k; R_Axial_DIN0207_L6.3mm_D2.5mm_P10.16mm_Horizontal
U1: Pico; RPi_Pico_SMD_TH
U2: ACS712xLCTR-20A; SOIC-8_3.9x4.9mm_P1.27mm
U4: AMS1117-5.0; SOT-223-3_TabPin2

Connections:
Bat+: C4.1, J1.1, R3.1, U2.1 (IP+), U2.2 (IP+), U4.3 (VI)
BuckOut: D3.1 (K), U2.3 (IP-), U2.4 (IP-)
Fuente 5V: C3.1, C5.1, J3.1, J4.3, J8.1, J9.2, U2.8 (VCC), U4.2 (VO)
Masa: C1.2, C2.2, C3.2, C4.2, C5.2, D1.2 (A), J1.2, J2.2, J3.2, J4.4, J5.1, J6.5, J7.5, J8.2, Q3.1 (C), Q4.3 (E), R2.2, R4.2, U1.3 (GND), U1.38 (GND), U2.5 (GND), U4.1 (GND)
unnamed: D1.1 (K), L1.1, Q1.2 (D)
unnamed: C2.1, D3.2 (A), L1.2
unnamed: J9.1, U1.39 (VSYS)
unnamed: Q1.1 (G), R5.2
unnamed: Q2.2 (B), Q3.2 (B), Q4.1 (C), R6.2
unnamed: Q2.3 (E), Q3.3 (E), R5.1
unnamed: Q4.2 (B), R7.2
unnamed: C1.1, U2.6 (FILTER)
Panel+: J2.1, Q1.3 (S), Q2.1 (C), R1.1, R6.1
Pi1: J6.4, J7.4, R1.2, R2.1, U1.31 (GPIO26_ADC0)
Pi2: J6.3, J7.3, R3.2, R4.1, U1.32 (GPIO27_ADC1)
Pi3: J6.2, J7.2, U1.34 (GPIO28_ADC2), U2.7 (VIOUT)
Pi4: J6.1, J7.1, R7.1, U1.20 (GPIO15)
Pi Rx: J5.2, U1.2 (GPIO1)
Pi SCL: U1.5 (GPIO3)
Pi SDA: U1.4 (GPIO2)
Pi Tx: J5.3, U1.1 (GPIO0)
PiSCL: J4.2
PiSDA: J4.1
